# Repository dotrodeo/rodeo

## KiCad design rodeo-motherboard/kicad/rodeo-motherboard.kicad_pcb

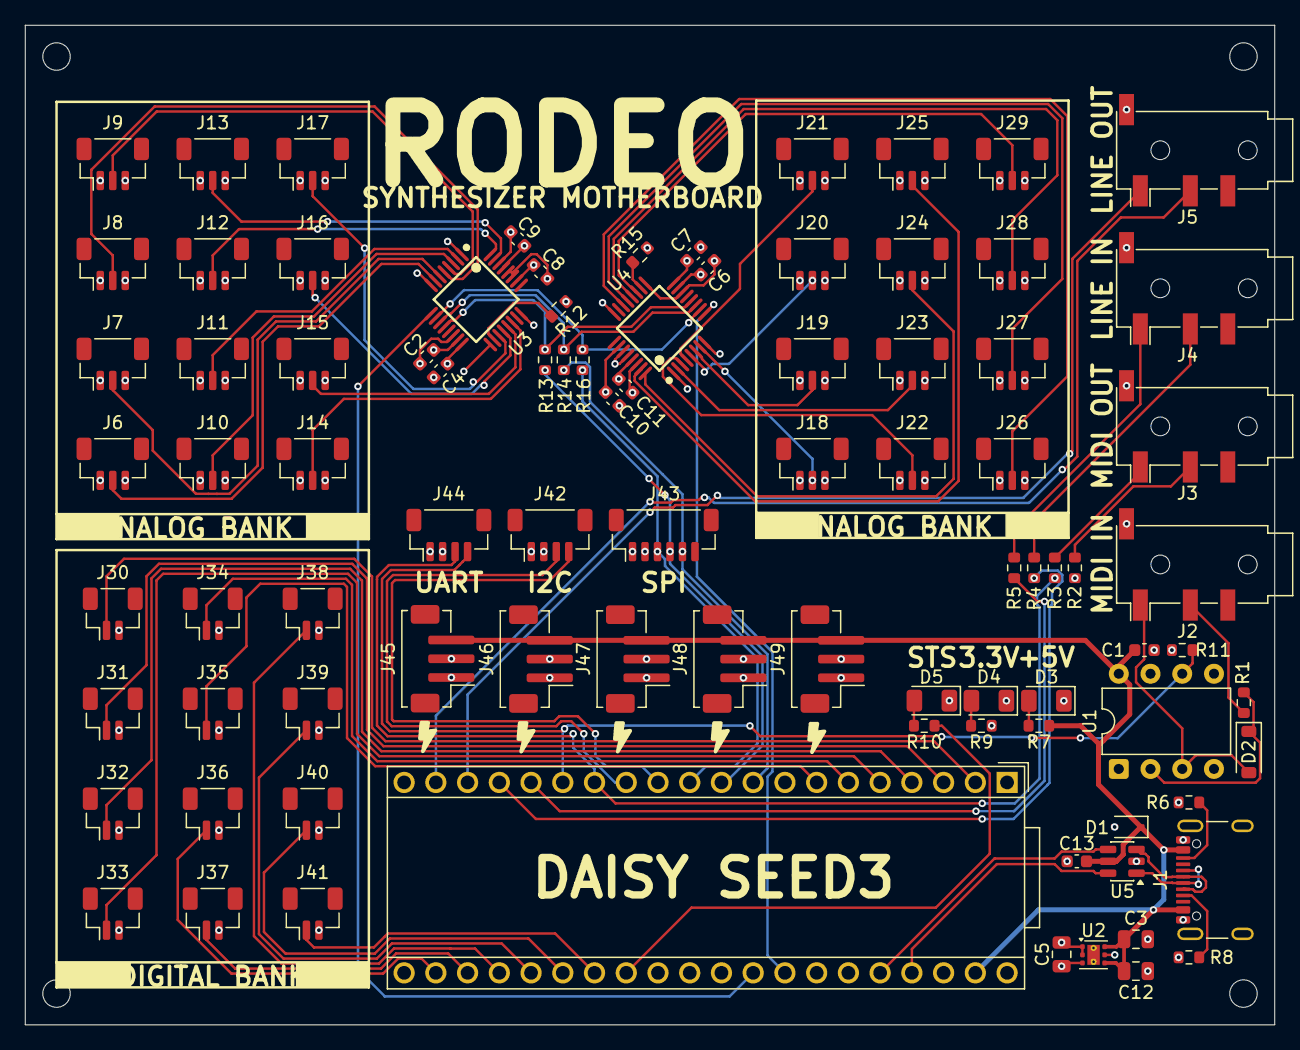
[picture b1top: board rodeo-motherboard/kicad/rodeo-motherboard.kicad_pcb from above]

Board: 4 copper layers, 100.0 x 80.0 mm, 89 parts (0 on the bottom side), 74 nets.

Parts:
A1: Electrosmith_Daisy_Seed_Rev4; Electrosmith_Daisy_Seed
C1, C2, C4, C6, C7, C13: 0.1u; C_0603_1608Metric
C3, C5: 1u; C_0805_2012Metric
C8, C10: 330n; C_0603_1608Metric
C9, C11: 1u; C_0603_1608Metric
C12: 22u; C_0805_2012Metric
D1: D_TVS; D_SOD-323
D2: 1N4148W; D_SOD-123
D3, D4, D5: LED; LED_1206_3216Metric
J1: USB_C_Receptacle; USB_C_Receptacle_GCT_USB4105-xx-A_16P_TopMnt_Horizontal
J2, J3, J4, J5: AudioJack4; Jack_3.5mm_PJ320D_Horizontal
J6, J7, J8, J9, J10, J11, J12, J13, J14, J15, J16, J17, J18, J19, J20, J21, J22, J23, J24, J25, J26, J27, J28, J29: Conn_01x03; JST_SH_BM03B-SRSS-TB_1x03-1MP_P1.00mm_Vertical
J30, J31, J32, J33, J34, J35, J36, J37, J38, J39, J40, J41: Conn_01x02; JST_SH_BM02B-SRSS-TB_1x02-1MP_P1.00mm_Vertical
J42: I2C; JST_SH_BM04B-SRSS-TB_1x04-1MP_P1.00mm_Vertical
J43: SPI; JST_SH_BM06B-SRSS-TB_1x06-1MP_P1.00mm_Vertical
J44: UART; JST_SH_BM04B-SRSS-TB_1x04-1MP_P1.00mm_Vertical
J45, J46, J47, J48, J49: Conn_01x03; JST_ZH_B3B-ZR-SM4-TF_1x03-1MP_P1.50mm_Vertical
R1: 220R; R_0603_1608Metric
R2, R3, R4, R5: 100R; R_0603_1608Metric
R6, R8: 5K1; R_0603_1608Metric
R7, R9, R10: 1K; R_0603_1608Metric
R11: 470R; R_0603_1608Metric
R12, R15: 10K; R_0603_1608Metric
R13, R14, R16: 33R; R_0603_1608Metric
U1: 6N138; DIP-8_W7.62mm
U2: TLV76733DRVx; WSON-6-1EP_2x2mm_P0.65mm_EP1x1.6mm_ThermalVias
U3, U4: TQFP-32_L5.0-W5.0-P0.50-LS7.0-BL
U5: USBLC6-2SC6; SOT-23-6

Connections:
+3V3: C2.1, C4.1, C5.1, C6.1, C7.1, C8.1, C9.2, C10.1, C11.2, J6.1, J7.1, J8.1, J9.1, J10.1, J11.1, J12.1, J13.1, J14.1, J15.1, J16.1, J17.1, J18.1, J19.1, J20.1, J21.1, J22.1, J23.1, J24.1, J25.1, J26.1, J27.1, J28.1, J29.1, J42.2, J43.1, J44.1, J45.2, J46.2, J47.2, J48.2, J49.2, R2.2, R9.2, R11.1, R12.2, R15.2, U2.1 (OUT), U2.2 (SNS), U3.8 (START/SYNC), U3.15 (IOVDD), U3.16 (DVDD), U3.26 (AVDD), U3.30 (REFP0), U4.8 (START/SYNC), U4.15 (IOVDD), U4.16 (DVDD), U4.26 (AVDD), U4.30 (REFP0)
ADC1_1: J6.2, U3.7 (AIN0)
ADC1_2: J7.2, U3.6 (AIN1)
ADC1_3: J8.2, U3.5 (AIN2)
ADC1_4: J9.2, U3.4 (AIN3)
ADC1_5: J10.2, U3.3 (AIN4)
ADC1_6: J11.2, U3.2 (AIN5)
ADC1_7: J12.2, U3.32 (REFP1/AIN6)
ADC1_8: J13.2, U3.31 (REFN1/AIN7)
ADC1_9: J14.2, U3.22 (GPIO0/AIN8)
ADC1_10: J15.2, U3.21 (GPIO1/AIN9)
ADC1_11: J16.2, U3.20 (GPIO2/AIN10)
ADC1_12: J17.2, U3.19 (GPIO3/AIN11)
ADC2_1: J18.2, U4.7 (AIN0)
ADC2_2: J19.2, U4.6 (AIN1)
ADC2_3: J20.2, U4.5 (AIN2)
ADC2_4: J21.2, U4.4 (AIN3)
ADC2_5: J22.2, U4.3 (AIN4)
ADC2_6: J23.2, U4.2 (AIN5)
ADC2_7: J24.2, U4.32 (REFP1/AIN6)
ADC2_8: J25.2, U4.31 (REFN1/AIN7)
ADC2_9: J26.2, U4.22 (GPIO0/AIN8)
ADC2_10: J27.2, U4.21 (GPIO1/AIN9)
ADC2_11: J28.2, U4.20 (GPIO2/AIN10)
ADC2_12: J29.2, U4.19 (GPIO3/AIN11)
ADC_MISO: R13.2, U3.12 (DOUT/DRDY#), U4.12 (DOUT/DRDY#)
ADC_MOSI: R16.2, U3.10 (DIN), U4.10 (DIN)
ADC_SCK: R14.2, U3.11 (SCLK), U4.11 (SCLK)
AUDIO_IN_L: A1.16 (AUDIO_IN_1), R5.1
AUDIO_IN_R: A1.17 (AUDIO_IN_2), R4.2
AUDIO_OUT_L+: A1.18 (AUDIO_OUT_1), J5.T
AUDIO_OUT_R+: A1.19 (AUDIO_OUT_2), J5.R1
DAISY_STATUS: A1.28 (ADC_6), R10.2
DIG_1: A1.2 (SD_DATA_3), J30.1
DIG_2: A1.3 (SD_DATA_2), J31.1
DIG_3: A1.4 (SD_DATA_1), J32.1
DIG_4: A1.5 (SD_DATA_0), J33.1
DIG_5: A1.6 (SD_CMD), J34.1
DIG_6: A1.7 (SD_CLK), J35.1
DIG_7: A1.22 (ADC_0), J36.1
DIG_8: A1.23 (ADC_1), J37.1
DIG_9: A1.24 (ADC_2), J38.1
DIG_10: A1.25 (ADC_3), J39.1
DIG_11: A1.26 (ADC_4), J40.1
DIG_12: A1.27 (ADC_5), J41.1
GND: A1.20 (AGND), A1.40 (DGND), C1.1, C2.2, C3.2, C4.2, C5.2, C6.2, C7.2, C8.2, C9.1, C10.2, C11.1, C12.2, C13.1, D1.2 (A2), D3.1 (K), D4.1 (K), D5.1 (K), J1.A1 (GND), J1.A12 (GND), J1.B1 (GND), J1.B12 (GND), J1.SH (SHIELD), J2.S, J3.S, J4.S, J5.S, J6.3, J7.3, J8.3, J9.3, J10.3, J11.3, J12.3, J13.3, J14.3, J15.3, J16.3, J17.3, J18.3, J19.3, J20.3, J21.3, J22.3, J23.3, J24.3, J25.3, J26.3, J27.3, J28.3, J29.3, J30.2, J31.2, J32.2, J33.2, J34.2, J35.2, J36.2, J37.2, J38.2, J39.2, J40.2, J41.2, J42.1, J43.2, J44.2, J45.1, J46.1, J47.1, J48.1, J49.1, R6.2, R8.2, U1.5 (GND), U2.3 (GND), U2.5 (GND), U2.7 (PAD), U3.1 (AINCOM), U3.14 (DGND), U3.17 (CLK), U3.24 (REFCOM), U3.27 (AVSS), U3.28 (AVSS), U3.29 (REFN0), U4.1 (AINCOM), U4.14 (DGND), U4.17 (CLK), U4.24 (REFCOM), U4.27 (AVSS), U4.28 (AVSS), U4.29 (REFN0), U5.2 (GND)
I2C_SCL: A1.12 (I2C1_SCL), J42.4
I2C_SDA: A1.13 (I2C1_SDA), J42.3
unnamed: D2.2 (A), J2.T, U1.3 (C2)
unnamed: D2.1 (K), R1.2, U1.2 (C1)
unnamed: D3.2 (A), R7.1
unnamed: D4.2 (A), R9.1
unnamed: D5.2 (A), R10.1
unnamed: J1.A5 (CC1), R8.1
unnamed: J1.B5 (CC2), R6.1
unnamed: J2.R1, R1.1
unnamed: J3.R1, R2.1
unnamed: J3.T, R3.1
unnamed: J4.R1, R4.1
unnamed: J4.T, R5.2
unnamed: R12.1, U3.18 (RESET#)
unnamed: R15.1, U4.18 (RESET#)
SPI_ADC1_CS: A1.32 (SAI2_SD_B), U3.9 (CS#)
SPI_ADC2_CS: A1.33 (SAI2_SD_A), U4.9 (CS#)
SPI_MISO: A1.10 (SPI1_POCI), J43.4, R13.1
SPI_MOSI: A1.11 (SPI1_PICO), J43.3, R16.1
SPI_SCK: A1.9 (SPI1_SCK), J43.5, R14.1
UART_RX: A1.15 (USART1_RX), J44.4, R11.2, U1.6 (VO2)
UART_TX: A1.14 (USART1_TX), J44.3, R3.2
USB_D+: A1.37 (USB_D_+), U5.6 (I/O1)
USB_D-: A1.36 (USB_D_-), U5.4 (I/O2)
USB_REC_D+: J1.A6 (D+), J1.B6 (D+), U5.1 (I/O1)
USB_REC_D-: J1.A7 (D-), J1.B7 (D-), U5.3 (I/O2)
VIN: A1.39 (VIN), C1.2, C3.1, C12.1, C13.2, D1.1 (A1), J1.A4 (VBUS), J1.A9 (VBUS), J1.B4 (VBUS), J1.B9 (VBUS), J45.3, J46.3, J47.3, J48.3, J49.3, R7.2, U1.8 (VCC), U2.4 (EN), U2.6 (IN), U5.5 (VBUS)

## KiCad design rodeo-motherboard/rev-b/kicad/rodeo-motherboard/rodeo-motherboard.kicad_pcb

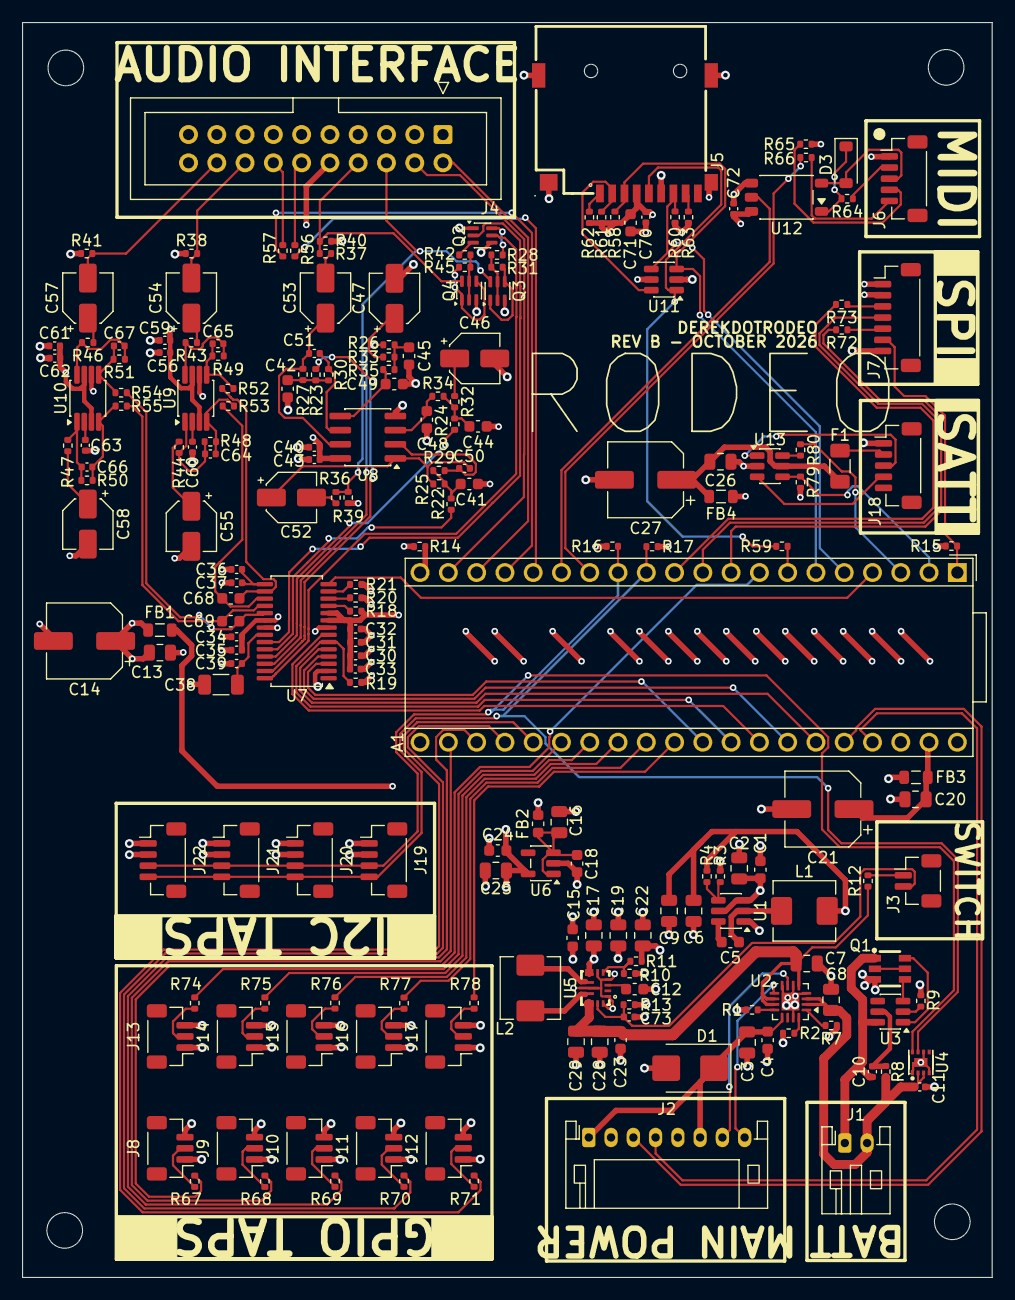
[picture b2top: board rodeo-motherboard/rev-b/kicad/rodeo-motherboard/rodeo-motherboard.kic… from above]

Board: 4 copper layers, 87.1 x 112.7 mm, 204 parts (0 on the bottom side), 147 nets.

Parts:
A1: Electrosmith_Daisy_Seed_Rev4; Electrosmith_Daisy_Seed
C1, C5: 0.1u; C_0603_1608Metric
C2, C3, C13, C16, C20, C25, C26, C28, C29: 10u; C_0805_2012Metric
C4, C18, C24: 1u; C_0603_1608Metric
C6, C9, C17, C19, C22: 22u; C_0805_2012Metric
C7, C8: 4.7u; C_0805_2012Metric
C10, C30, C32, C34, C37, C39, C43, C59, C60, C62, C63, C70, C72: 0.1u; C_0402_1005Metric
C11, C31, C33, C35, C36, C40, C56, C61: 1u; C_0402_1005Metric
C12: 100n; C_0603_1608Metric
C14, C21, C27: 100u; CP_Elec_6.3x5.4
C15, C23, C71: 10u; C_0603_1608Metric
C38: 47u; C_1206_3216Metric
C41, C42: 2.2n; C_0603_1608Metric
C44, C45: 6.8n; C_0603_1608Metric
C46, C47, C52, C53: 22u; CP_Elec_4x5.4
C48, C49: 1.5n; C_0603_1608Metric
C50, C51: 470p; C_0402_1005Metric
C54, C55, C57, C58: 10u; CP_Elec_4x5.4
C64, C65, C66, C67: 150p; C_0402_1005Metric
C68, C69: 2.7n; C_0603_1608Metric
C73: 10n; C_0402_1005Metric
D1: SMBJ5.0A; D_SMB
D3: 1N4148W; D_SOD-123
F1: nSMD075; Fuse_1206_3216Metric
FB1, FB3, FB4: BLM21PG221SN1D; L_0805_2012Metric
FB2: BLM18KG601SN1D; L_0603_1608Metric
H1, H2, H3, H4: MountingHole; MountingHole_3.2mm_M3
J1: Conn_01x02; JST_PH_S2B-PH-K_1x02_P2.00mm_Horizontal
J2: Conn_01x08; JST_PH_S8B-PH-K_1x08_P2.00mm_Horizontal
J3: Conn_01x02; JST_SH_BM02B-SRSS-TB_1x02-1MP_P1.00mm_Vertical
J4: Conn_02x10_Odd_Even; IDC-Header_2x10_P2.54mm_Vertical
J5: TF PUSH; TF-SMD_TF-PUSH
J6, J18: Conn_01x05; JST_SH_BM05B-SRSS-TB_1x05-1MP_P1.00mm_Vertical
J7: Conn_01x07; JST_SH_BM07B-SRSS-TB_1x07-1MP_P1.00mm_Vertical
J8, J9, J10, J11, J12, J13, J14, J15, J16, J17: Conn_01x03; JST_SH_BM03B-SRSS-TB_1x03-1MP_P1.00mm_Vertical
J19, J20, J21, J22: Conn_01x04; JST_SH_BM04B-SRSS-TB_1x04-1MP_P1.00mm_Vertical
L1: 2.2uH; L_Sunlord_MWSA0518S
L2: 1.5uH; L_Sunlord_MWSA0518S
Q1: FS8205A; SOT-23-6_L2.9-W1.6-P0.95-LS2.8-BR
Q2: BSS84DW; SOT-363_SC-70-6
Q3, Q4: 2N7002DW; SOT-363_SC-70-6
R1: 1.18K; R_0402_1005Metric
R2: 1.13K; R_0402_1005Metric
R3, R7, R12, R15, R18, R20, R21, R28, R42, R79: 10K; R_0402_1005Metric
R4: 33K2; R_0402_1005Metric
R8, R56, R57, R65, R66: 100R; R_0402_1005Metric
R9, R67, R68, R69, R70, R71, R74, R75, R76, R77, R78: 1K; R_0402_1005Metric
R10: 19K1; R_0402_1005Metric
R11: 100K; R_0402_1005Metric
R13, R31, R38, R41, R45: 1M; R_0402_1005Metric
R14: 0R; R_0402_1005Metric
R16, R17: 2K2; R_0402_1005Metric
R19, R39, R40, R58, R60, R61, R62, R63: 47K; R_0402_1005Metric
R22, R23: 4K42; R_0402_1005Metric
R24, R26: 1K33; R_0402_1005Metric
R25, R27: 4K99; R_0402_1005Metric
R29, R30: 2K32; R_0402_1005Metric
R32, R33: 1K5; R_0402_1005Metric
R34, R35: 715R; R_0402_1005Metric
R36, R37: 560R; R_0402_1005Metric
R43, R44, R46, R47: 7K5; R_0402_1005Metric
R48, R49, R50, R51: 10K5; R_0402_1005Metric
R52, R53, R54, R55: 91R; R_0402_1005Metric
R59: 22R; R_0402_1005Metric
R64: 220R; R_0402_1005Metric
R72, R73, R80: 33R; R_0402_1005Metric
U1: TPS563208; TSOT-23-6
U2: BQ24073RGT; VQFN-16-1EP_3x3mm_P0.5mm_EP1.6x1.6mm
U3: DW01A; SOT-23-6
U4: MAX17048G+T10; TDFN-8_L2.0-W2.0-P0.50-BL-EP1.2
U5: TPS63070RNMR; VQFN-15_L3.0-W2.5-P0.50-BL
U6: TPS7A2033PDBVR; SOT-23-5
U7: CS4272; TSSOP-28_4.4x9.7mm_P0.65mm
U8: OPA2376xxD; SOIC-8_3.9x4.9mm_P1.27mm
U9, U10: THS4521IDGK; VSSOP-8_3x3mm_P0.65mm
U11: SRV05-4; SOT-23-6
U12: TLP2361; SO-5-6_4.55x3.7mm_P1.27mm
U13: USBLC6-2SC6; SOT-23-6

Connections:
+3V3_A: C24.2, C25.2, J7.7, J8.3, J9.3, J10.3, J11.3, J12.3, J13.3, J14.3, J15.3, J16.3, J17.3, U6.5 (OUT)
+3V3_D: C6.2, C9.2, C30.2, C31.2, C32.2, C33.2, C70.1, C71.1, C72.2, FB4.1, J5.4 (VDD), J7.1, J19.2, J20.2, J21.2, J22.2, L1.2, R4.2, R15.2, R16.1, R17.1, R18.2, R58.1, R60.1, R61.1, R62.1, R63.1, R65.2, R79.2, U7.9 (VD), U7.10 (VL), U11.5 (VP), U12.6 (VDD)
+3V3_SAT: C26.2, C27.1, F1.2, FB4.2, U13.5 (VBUS)
+5V_A: C13.2, C14.1, C34.2, C35.2, C40.2, C43.1, C56.2, C59.1, C61.2, C62.1, FB1.2, J4.10, Q2.1 (S), Q2.4 (S), U7.20 (VA), U8.8 (V+), U9.3 (V_{S+}), U9.7 (~PD), U10.3 (V_{S+}), U10.7 (~PD)
+5V_SYS: C1.1, C2.1, C15.1, C17.1, C19.1, C22.1, FB1.1, FB2.1, FB3.1, R11.2, U1.3 (VIN), U1.5 (EN), U5.7 (Vout)
AUDIO_IN_1: A1.16 (AUDIO_IN_1), R56.1
AUDIO_IN_2: A1.17 (AUDIO_IN_2), R57.1
AUDIO_OUT_1: A1.18 (AUDIO_OUT_1), J4.2
AUDIO_OUT_2: A1.19 (AUDIO_OUT_2), J4.4
BATT_N: C10.1, J1.1, Q1.1 (S1), U3.6 (GND)
BATT_P: C8.1, C11.1, J1.2, R8.1, U2.2 (BAT), U2.3 (BAT), U4.2 (CELL), U4.3 (VDD)
BATT_VCC: C7.1, C23.1, C28.1, C29.1, R12.1, U2.5 (EN2), U2.10 (OUT), U2.11 (OUT), U5.12 (Vin)
CLK: J5.5 (CLK), R59.1, U11.1 (IO1)
CODEC2_AINA_N: C68.2, R52.1, U7.16 (AINA-)
CODEC2_AINA_P: C68.1, R53.1, U7.17 (AINA+)
CODEC2_AINB_N: C69.2, R54.1, U7.19 (AINB-)
CODEC2_AINB_P: C69.1, R55.1, U7.18 (AINB+)
CODEC2_AOUTA_N: R22.1, U7.24 (AOUTA-)
CODEC2_AOUTA_P: R24.1, U7.25 (AOUTA+)
CODEC2_AOUTB_N: R23.1, U7.27 (AOUTB-)
CODEC2_AOUTB_P: R26.1, U7.26 (AOUTB+)
CODEC2_IN_A: C54.2, J4.16, R38.2
CODEC2_IN_B: C57.2, J4.18, R41.2
CODEC2_LRCK: A1.34 (SAI2_FS), U7.4 (LRCK)
CODEC2_MCLK: A1.31 (SAI2_MCLK), U7.3 (MCLK)
CODEC2_MUTE_A: Q2.2 (G), U7.23 (~AMUTEC)
CODEC2_MUTE_B: Q2.5 (G), U7.28 (~BMUTEC)
CODEC2_OUT_A: J4.6, Q3.6 (D), R36.1, R39.1
CODEC2_OUT_B: J4.8, Q4.6 (D), R37.1, R40.1
CODEC2_RST: A1.4 (SD_DATA_1), U7.14 (~RST)
CODEC2_SCLK: A1.35 (SAI2_SCK), U7.5 (SCLK)
CODEC2_SDIN: A1.33 (SAI2_SD_A), U7.7 (SDIN)
CODEC2_SDOUT: A1.32 (SAI2_SD_B), R19.2, U7.6 (SDOUT(M/~S))
CODEC2_VCOM: C36.2, C37.2, U7.15 (VCOM)
CV_DAC1: A1.30 (DAC_OUT1), R78.2
CV_DAC2: A1.29 (DAC_OUT2), R77.2
DAISY_SCL: A1.12 (I2C1_SCL), J19.4, J20.4, J21.4, J22.4, R17.2, U4.7 (SCL)
DAISY_SDA: A1.13 (I2C1_SDA), J19.3, J20.3, J21.3, J22.3, R16.2, U4.8 (SDA)
DAT3: J5.2 (CD/DAT3), R61.2, U11.6 (IO4)
DIG_1: A1.8 (SPI1_CS), R67.2
DIG_2: A1.22 (ADC_0), R68.2
DIG_3: A1.23 (ADC_1), R69.2
DIG_4: A1.24 (ADC_2), R70.2
DIG_5: A1.25 (ADC_3), R71.2
DIG_6: A1.26 (ADC_4), R74.2
DIG_7: A1.27 (ADC_5), R75.2
DIG_8: A1.28 (ADC_6), R76.2
GND: A1.40 (DGND), C1.2, C2.2, C3.2, C4.2, C6.1, C7.2, C8.2, C9.1, C11.2, C12.2, C13.1, C14.2, C15.2, C16.1, C17.2, C18.1, C19.2, C20.1, C21.2, C22.2, C23.2, C24.1, C25.1, C26.1, C27.2, C28.2, C29.2, C30.1, C31.1, C32.1, C33.1, C34.1, C35.1, C36.1, C37.1, C38.2, C39.1, C40.1, C41.2, C42.2, C43.2, C44.1, C45.1, C46.2, C47.2, C48.2, C49.2, C55.2, C56.1, C58.2, C59.2, C60.2, C61.1, C62.2, C63.2, C70.2, C71.2, C72.1, C73.1, D1.2 (A), J2.2, J2.5, J4.1, J4.3, J4.5, J4.7, J4.9, J4.11, J4.13, J4.15, J4.17, J4.19, J5.6 (VSS), J5.10, J5.11, J5.12, J5.13, J6.1, J7.2, J8.1, J9.1, J10.1, J11.1, J12.1, J13.1, J14.1, J15.1, J16.1, J17.1, J18.1, J19.1, J20.1, J21.1, J22.1, Q1.3 (S2), Q3.3 (D), Q4.3 (D), R1.1, R2.1, R3.1, R7.2, R9.2, R10.1, R13.2, R14.1, R19.1, R20.2, R21.2, R38.1, R39.2, R40.2, R41.1, U1.1 (GND), U2.4 (~CE), U2.6 (EN1), U2.8 (VSS), U2.15 (TD), U2.17 (VSS), U4.1 (CTG), U4.4 (GND), U4.6 (QSTRT), U4.9 (EP), U5.1 (PS/SYNC), U5.4 (GND), U5.6 (FB2), U5.10 (PGND), U5.15 (Vsel), U6.2 (GND), U7.2 (XTI), U7.8 (DGND), U7.21 (AGND), U8.4 (V-), U9.6 (V_{S-}), U10.6 (V_{S-}), U11.2 (VN), U12.4 (GND), U13.2 (GND)
GNDA: A1.20 (AGND), R14.2
JACK_IN_1: J4.12, R56.2
JACK_IN_2: J4.14, R57.2
MIDI_IN_R: J6.2, R64.1
MIDI_IN_T: D3.2 (A), J6.3, U12.3 (K)
MIDI_OUT_R: J6.4, R65.1
MIDI_OUT_T: J6.5, R66.1
MIDI_RX: A1.15 (USART1_RX), U12.5 (VO)
MIDI_TX: A1.14 (USART1_TX), R66.2
unnamed: C41.1, R22.2, R25.1, R29.1
unnamed: C42.1, R23.2, R27.1, R30.1
unnamed: C44.2, R24.2, R32.2, R34.2
unnamed: C45.2, R26.2, R33.2, R35.2
unnamed: C46.1, R32.1
unnamed: C47.1, R33.1
unnamed: C50.1, C52.1, R25.2, U8.1
unnamed: C51.1, C53.1, R27.2, U8.7
unnamed: C52.2, R36.2
unnamed: C53.2, R37.2
unnamed: C54.1, R43.1
unnamed: C55.1, R44.1
unnamed: C57.1, R46.1
unnamed: C58.1, R47.1
unnamed: C64.2, R48.2, R53.2, U9.4
unnamed: C65.1, R49.2, R52.2, U9.5
unnamed: C66.2, R50.2, R55.2, U10.4
unnamed: C67.1, R51.2, R54.2, U10.5
unnamed: D3.1 (K), R64.2, U12.1 (A)
unnamed: J3.1, R12.2
unnamed: C73.2, J3.2, R13.1, U5.14 (EN)
unnamed: J5.8 (DAT1), R63.2
unnamed: J5.1 (DAT2), R62.2
unnamed: J7.3, R73.1
unnamed: J7.5, R72.1
unnamed: J8.2, R67.1
unnamed: J9.2, R68.1
unnamed: J10.2, R69.1
unnamed: J11.2, R70.1
unnamed: J12.2, R71.1
unnamed: J13.2, R74.1
unnamed: J14.2, R75.1
unnamed: J15.2, R76.1
unnamed: J16.2, R77.1
unnamed: J17.2, R78.1
unnamed: F1.1, J18.2
unnamed: J18.3, U13.1 (I/O1)
unnamed: J18.4, U13.3 (I/O2)
unnamed: Q1.2 (D1/D2), Q1.5 (D1/D2)
unnamed: Q1.6 (G1), U3.1 (OD)
unnamed: Q1.4 (G2), U3.3 (OC)
unnamed: Q2.6 (D), R28.2
unnamed: Q2.3 (D), R42.2
unnamed: Q3.2 (G), Q3.5 (G), R28.1, R31.1
unnamed: Q3.1 (S), Q3.4 (S), R31.2
unnamed: Q4.2 (G), Q4.5 (G), R42.1, R45.1
unnamed: Q4.1 (S), Q4.4 (S), R45.2
unnamed: R80.1, U13.6 (I/O1)
unnamed: C5.2, L1.1, U1.2 (SW)
unnamed: C5.1, U1.6 (VBST)
unnamed: R3.2, R4.1, U1.4 (VFB)
unnamed: R1.2, U2.12 (ILIM)
unnamed: R2.2, U2.16 (ISET)
unnamed: R7.1, U2.1 (TS)
unnamed: R9.1, U3.2 (CS)
unnamed: C10.2, R8.2, U3.5 (VCC)
unnamed: R10.2, R11.1, U5.5 (FB)
unnamed: L2.1, U5.11 (L1)
unnamed: L2.2, U5.9 (L2)
unnamed: C12.1, U5.3 (Vaux)
unnamed: C16.2, C18.2, FB2.2, U6.1 (IN), U6.3 (EN)
unnamed: R21.1, U7.13 (AD0/~CS(I2S/~LJ))
unnamed: C38.1, C39.2, U7.22 (FILT+)
unnamed: R18.1, U7.11 (SCL/CCLK(M0))
unnamed: R20.1, U7.12 (SDA/CDIN(M1))
unnamed: C48.1, R34.1, U8.3 (+)
unnamed: C50.2, R29.2, U8.2 (-)
unnamed: C49.1, R35.1, U8.5 (+)
unnamed: C51.2, R30.2, U8.6 (-)
unnamed: C65.2, R43.2, R49.1, U9.8 (+)
unnamed: C64.1, R44.2, R48.1, U9.1 (-)
unnamed: C60.1, U9.2 (V_{OCM})
unnamed: C67.2, R46.2, R51.1, U10.8 (+)
unnamed: C66.1, R47.2, R50.1, U10.1 (-)
unnamed: C63.1, U10.2 (V_{OCM})
SAT_RX: A1.2 (SD_DATA_3), R79.1, U13.4 (I/O2)
SAT_TX: A1.3 (SD_DATA_2), R80.2
SD_CLK: A1.7 (SD_CLK), R59.2
SD_CMD: A1.6 (SD_CMD), J5.3 (CMD), R58.2, U11.3 (IO2)
SD_D_0: A1.5 (SD_DATA_0), J5.7 (DAT0), R60.2, U11.4 (IO3)
SEED_VIN: A1.39 (VIN), C20.2, C21.1, FB3.2
SPI_EXT_CS: A1.1 (USB_ID), J7.6, R15.1
SPI_MISO: A1.10 (SPI1_POCI), J7.4
SPI_MOSI: A1.11 (SPI1_PICO), R73.2
SPI_SCK: A1.9 (SPI1_SCK), R72.2
USB_OTG_HS_N: A1.36 (USB_D_-), J2.3
USB_OTG_HS_P: A1.37 (USB_D_+), J2.4
VIN: C3.1, C4.1, D1.1 (K), J2.1, J2.6, U2.13 (IN)
~CHG: J2.8, U2.9 (~CHG)
~PGOOD: J2.7, U2.7 (~PGOOD)
